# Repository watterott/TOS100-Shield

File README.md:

# TOS100-Shield
Shield for Arduino to drive stepper motors.

* [Trinamic](https://www.trinamic.com) stepper motor driver (chopper drive / constant current drive)
* Open-Source and released under the [Creative Commons Attribution Share-Alike License](https://creativecommons.org/licenses/by-sa/4.0/).
* Based on the original [TOS-100-Shield](https://github.com/trinamic/TOS-100) from Trinamic
* **[Documentation on learn.watterott.com](https://learn.watterott.com)**

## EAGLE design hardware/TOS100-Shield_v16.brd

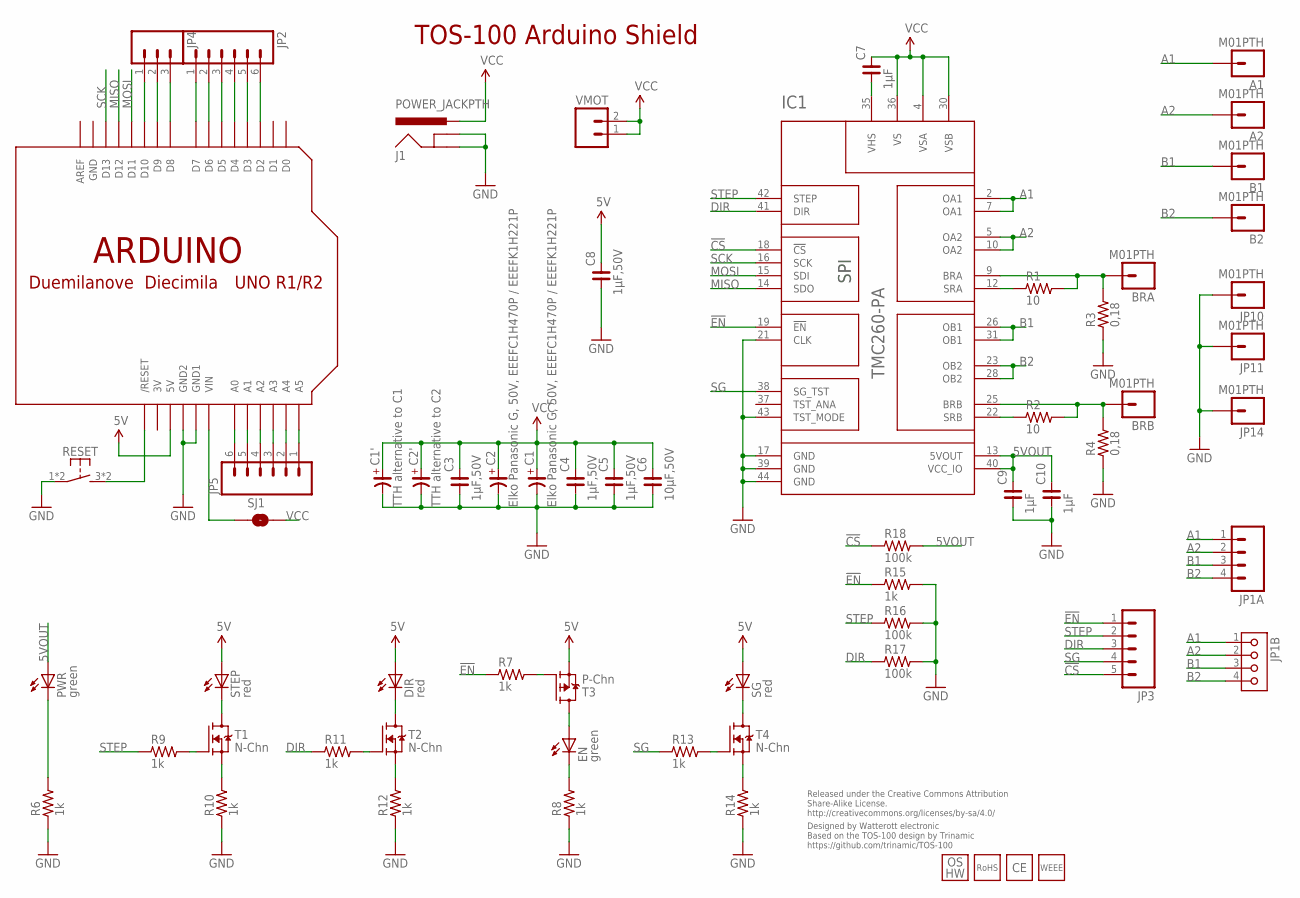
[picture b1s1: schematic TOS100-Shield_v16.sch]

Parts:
A1, A2: M01PTH; 1X01
ARD: ARDUINOUNO; ARDUINO
B1, B2: M01PTH; 1X01
BRA: M01PTH; 1X01
BRB: M01PTH; 1X01
C1, C2: Elko Panasonic G, 50V, EEEFC1H470P / EEEFK1H221P; CSV-G
C1': TTH alternative to C1; CE-035X100
C2': TTH alternative to C2; CE-035X100
C3, C4, C5, C8: 1µF,50V; C0603
C6: 10µF,50V; C1206
C7, C9, C10: 1µF; C0603
DIR: red; C0603
EN: green; C0603
IC1: TMC260-PA; PQFP44_WITH_PADS
J1: POWER_JACKPTH; POWER_JACK_PTH
JP1A: M04SCREW; SCREWTERMINAL-3.5MM-4
JP1B: KK4H; KK-H-4
JP2, JP5: M06SIP; 1X06
JP3: M05PTH; 1X05
JP4: M03PTH; 1X03
JP10, JP11, JP14: M01PTH; 1X01
LOGO1: LOGO_OSHW-5; OSHW_5MM
LOGO2: LOGO_CE-2; CE_2MM
LOGO3: LOGO_WEEE-4; WEEE_4MM
LOGO4: LOGO_ROHS-2; ROHS_2MM
PWR: green; C0603
R1, R2: 10; R0603
R3, R4: 0,18; R2512
R6, R7, R8, R9, R10, R11, R12, R13, R14, R15: 1k; R0603
R16, R17, R18: 100k; R0603
RESET: PTS645SH50SMTR92-Grey; SW6X6_SMD
SG: red; C0603
SJ1: SOLDERJUMPERNO; SJ_2S-NO
STEP: red; C0603
T1, T2, T4: N-Chn; SOT23
T3: P-Chn; SOT23
VMOT: M021X02_NO_SILK; 1X02_NO_SILK

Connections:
3V: ARD.3V
5V: ARD.5V, C8.2, DIR.A, SG.A, STEP.A, T3.2 (S)
5VOUT: C9.2, C10.2, IC1.13 (5VOUT), IC1.40 (VCC_IO), PWR.A, R18.2
!CS: IC1.18 (!CS), JP3.5, R18.1
!EN: IC1.19 (!EN), JP3.1, R7.1, R15.1
A1: A1.1, IC1.2 (OA1), IC1.7 (OA1), JP1A.1, JP1B.1
A2: A2.1, IC1.5 (OA2), IC1.10 (OA2), JP1A.2, JP1B.2
B1: B1.1, IC1.26 (OB1), IC1.31 (OB1), JP1A.3, JP1B.3
B2: B2.1, IC1.23 (OB2), IC1.28 (OB2), JP1A.4, JP1B.4
DIR: IC1.41 (DIR), JP3.3, R11.1, R17.1
GND: ARD.GND, ARD.GND1, ARD.GND2, C1.-, C1'.-, C2.-, C2'.-, C3.1, C4.1, C5.1, C6.1, C8.1, C9.1, C10.1, IC1.17 (GND), IC1.21 (CLK), IC1.39 (GND), IC1.43 (TST_MODE), IC1.44 (GND), J1.GND, J1.GNDBREAK, JP10.1, JP11.1, JP14.1, R3.1, R4.1, R6.1, R8.1, R10.1, R12.1, R14.1, R15.2, R16.2, R17.2, RESET.1, RESET.2 (P1)
MISO: ARD.D12, IC1.14 (SDO)
MOSI: ARD.D11, IC1.15 (SDI)
unnamed: ARD.D10, JP4.1
unnamed: ARD.D9, JP4.2
unnamed: ARD.D8, JP4.3
unnamed: ARD.D7, JP2.1
unnamed: ARD.D6, JP2.2
unnamed: ARD.D5, JP2.3
unnamed: ARD.D4, JP2.4
unnamed: ARD.D3, JP2.5
unnamed: ARD.D2, JP2.6
unnamed: ARD.A5, JP5.1
unnamed: ARD.A4, JP5.2
unnamed: ARD.A3, JP5.3
unnamed: ARD.A2, JP5.4
unnamed: ARD.A1, JP5.5
unnamed: ARD.A0, JP5.6
unnamed: R9.2, T1.1 (G)
unnamed: ARD.RESET (/RESET), RESET.3 (S1), RESET.4 (S1)
unnamed: STEP.C, T1.3 (D)
unnamed: R10.2, T1.2 (S)
unnamed: PWR.C, R6.2
unnamed: R11.2, T2.1 (G)
unnamed: DIR.C, T2.3 (D)
unnamed: R12.2, T2.2 (S)
unnamed: EN.A, T3.3 (D)
unnamed: BRA.1, IC1.9 (BRA), R1.2, R3.2
unnamed: IC1.12 (SRA), R1.1
unnamed: BRB.1, IC1.25 (BRB), R2.2, R4.2
unnamed: IC1.22 (SRB), R2.1
unnamed: EN.C, R8.2
unnamed: R7.2, T3.1 (G)
unnamed: R13.2, T4.1 (G)
unnamed: SG.C, T4.3 (D)
unnamed: R14.2, T4.2 (S)
SCK: ARD.D13, IC1.16 (SCK)
SG: IC1.38 (SG_TST), JP3.4, R13.1
STEP: IC1.42 (STEP), JP3.2, R9.1, R16.1
VCC: C1.+, C1'.+, C2.+, C2'.+, C3.2, C4.2, C5.2, C6.2, C7.2, IC1.4 (VSA), IC1.30 (VSB), IC1.36 (VS), J1.PWR, SJ1.2, VMOT.1, VMOT.2
VHS: C7.1, IC1.35 (VHS)
VIN: ARD.VIN, SJ1.1

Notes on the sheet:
TOS-100 Arduino Shield
Released under the Creative Commons Attribution Share-Alike License. http://creativecommons.org/licenses/by-sa/4.0/
Designed by Watterott electronic Based on the TOS-100 design by Trinamic https://github.com/trinamic/TOS-100

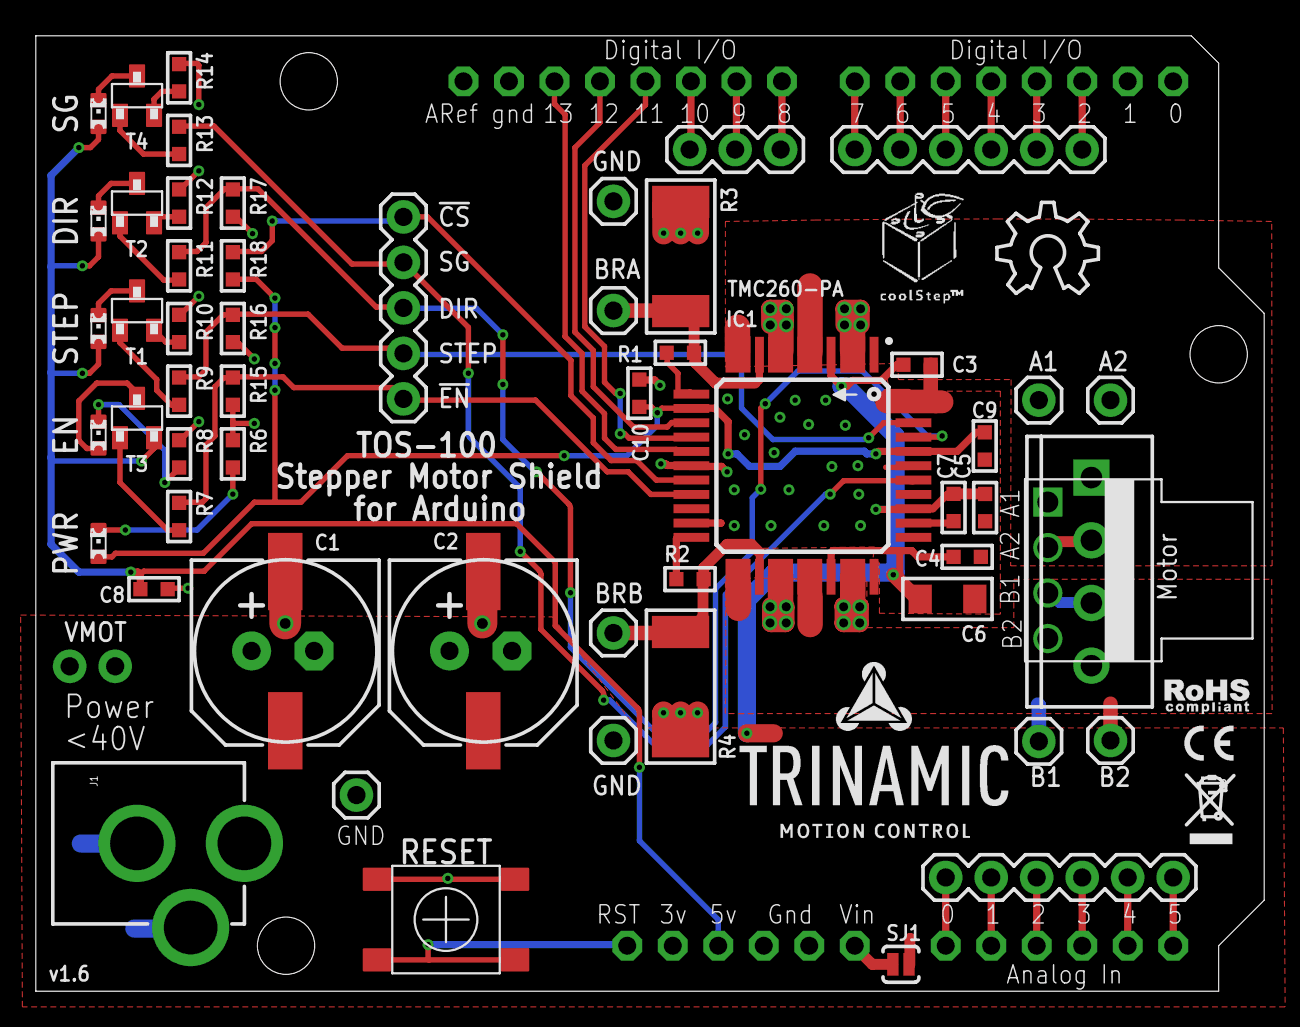
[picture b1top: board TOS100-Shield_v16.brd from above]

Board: 2 copper layers, 68.6 x 53.3 mm, 65 parts (0 on the bottom side), 51 nets.

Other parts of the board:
U$5: LOGO
U$9: COOLSTEP

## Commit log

2019-03-23 added layout and schematics
2019-03-23 added readme
2019-03-27 updated layout and schematics
2019-05-12 updated silkscreen
